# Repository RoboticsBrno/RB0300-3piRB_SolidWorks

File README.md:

# SOČ 2016 - Nadstavbová deska pro robota Pololu 3pi
**Autor:** Petr Bobčík

Vítejte v příloze mé práce Nadstavbová deska pro robota Pololu 3pi

#### V této příloze naleznete: 
1) Dokumenty
1) Eagle
1) Obhajoba
1) Použité obrázky
1) SolidWorks

#### Podrobnější obsah jednotlivých složek:
1) Přehled projektu s grafm pro IR senzor, obrázek s konceptem zapojení a tabulku potřebných součástek na pájení.
2) Finální verze desky a schéma k ní v programu Eagle + schéma s deskou k nárazovému senzoru.
3) Text samotné sočky a prezentaci k ní.
4) Veškeré obrázky použity jak v prezentaci, tak v textové práci.
5) Kompletní 3D model robota Pololu 3pi s přídavným shieldem.

## Cíl práce
<p>Cílem této práce byl návrh nadstavbové desky (shieldu) pro robota Pololu 3pi. Konstrukce robota je od výrobce optimalizována
na soutěžní disciplínu „sledování čáry“, kde robot dosahuje výborných výsledků a nemá mezi komerčně dostupnými produkty konkurenci. Ovšem při složitější variantě této disciplíny “najdi čáru“, konající se na Robotickém dni v Praze, kde dráha obsahuje rozpojky, odbočky, nebo překážky, není možné s ním závodit. Můj shield může posloužit, kromě možné účasti na soutěžích, také ve výuce. V ní si student může
robota sám naprogramovat. Přidáním funkcí a senzorů bude robot univerzálnější než doposud.</p>

<p>Práce řeší rozšíření možností využití robota Pololu 3pi návrhem nadstavby s doplňkovými funkcemi.
Přidané funkce umožňují robotovi snímat podněty ze svého okolí. Další navrženou částí je nárazník pro ochranu před mechanickým poškozením, ke kterému v praxi velmi často dochází. Tyto nárazy způsobovli nefunkčnost senzorů odrazivosti nebo dokonce i jejich odlomení od desky.</p>

Můj přídavný shield je také pinově kompatibilní s bastlířskými deskami, jako je **Arduino Uno**, **FRDM-KL25Z**, **FRDM-KL46Z** a **FRDM-K64F**. Je tedy možné a plánované, že pro přidání dalších funkcí, které můj shield neobsahuje, je možné připevnit jednu ze zmíněných desek, nebo desku, která má shodný pinout. Mikrokontroler, ATmega328P, který je na základním modelu robota se využívá jako MCU pro motory a hlavní řídící mikrokontroler je AVR XMEGu A1, který se nachází na mém shieldu. Ten mi poskytuje velký počet pinů s potřebnými periferiemi. 

## Jaké funkce jsou prostřednictvím shieldu přidány?
<p>Tato práce přidává robotovi Pololu 3pi schopnost detekovat překážku pomocí IR senzorů, kterých je na shieldu celkem 8 po 45° nebo pomocí nárazového senzoru, upevněného na mnou navržený nárazník. Dále také k orientaci v prostoru je přidáno IMU (inerciální pohybová jednotka), která obsahuje gyroskop, magnetometr a akcelerometr v jednom pouzdře. Posledním senzorem je enkodér, pomocí kterého můžeme měřit ujetou vzdálenost, zajišťuje přesnější otáčení okolo osi a umožňuje také měřit rychlost.</p><p>Na desce je přidán také chip pro nabíjení baterií, takže není zapotřebí vytahovat tužkové baterie, které se na základní verzi robota nacházejí. Pouzdra s tužkovými bateriemi je tedy možné vytáhnout a tím snížit váhu. Shield také obsahuje obvod pro měření baterie a to jak napětí, tak proudu. Tímto měřením je možné hlídat úroveň nabití baterie nebo dokonce detekovat, zda baterie není poškozená.</p>

## Co je vlastě Pololu 3pi? 
<p>Je to velmi rychlý komerčně dostupný soutěžní robot, určený na disciplínu s názvem sledování čáry, která je v České republice velmi populární (tato disciplína je více popsaná níže). Jeho průměr je 95 mm (odtud dostal název 3pi) a hmotnost 83 g (bez baterií). Jeho rychlost se pohybuje okolo 1m/s. Hlavním mozkem celého robota je mikrokontrolér ATmega328P, který se nachází například u Arduino Nano. Tento robot je vhodný pro začínající programátory, kteří se chtějí od začátečních robotů, jako například legových ze stavebnice Mindstorm, posunout o kousek dále a chtějí se naučit programovací.</p>

## Sledování čáry
</p>Úkolem robota je, aby následoval černou čářu, která se pod ním nachází. Nejprve šlo jen o jízdu po čáře, ale v poslední době se zmíněná disciplína výrazně ztížila, přidáním rozdvojení, křižovatky, přerušení a překážky. Pololu 3pi nedokáže tyto nové prvky řešit, a proto jsem se rozhodl přidat potřebné funkce, které to zajistí.<p>

#### [Více informací naleznete na stránkách Robotárny k mojí SOČ](https://www.robotikabrno.cz/robotarna/projekty-a-socky/soc-2017-petr-bobcik-nadstavbova-deska-pro-robota-pololu-3pi). 

Tato práce byla vypracována společně s [Robotárnou](www.robotarna.cz) a [SPŠ a VOŠ Sokolská Brno](www.spssbrno.cz).

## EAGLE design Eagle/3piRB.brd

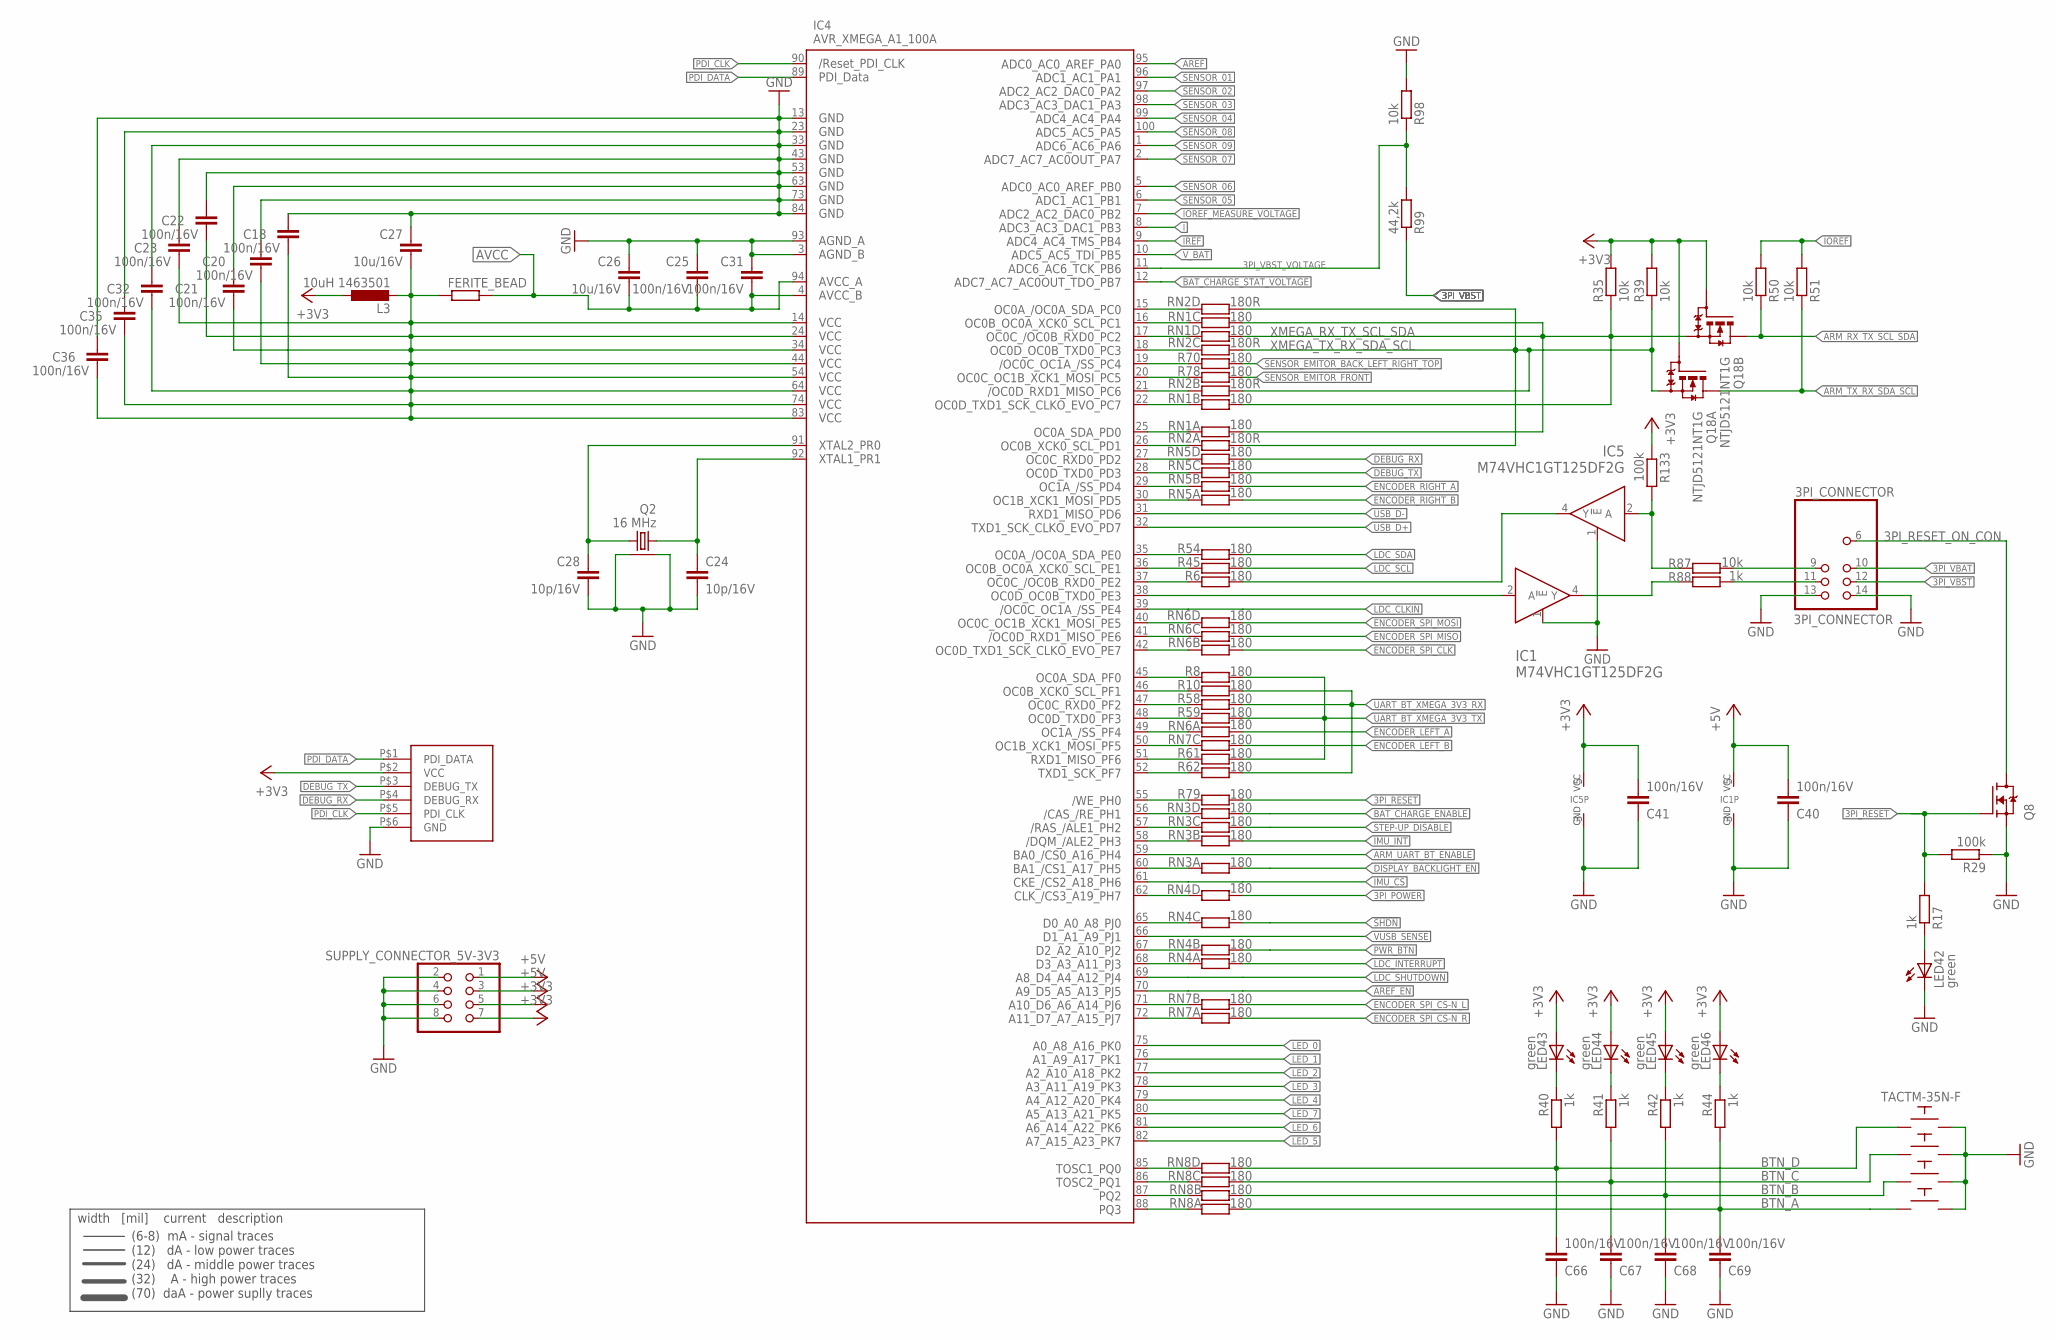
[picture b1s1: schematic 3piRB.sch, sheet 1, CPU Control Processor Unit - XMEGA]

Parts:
3PI_CONNECTOR: 3PI_CONNECTOR; 3PI_BT_CONNECTOR
BTN_A: TACTM-35N-F
BTN_B: TACTM-35N-F
BTN_C: TACTM-35N-F
BTN_D: TACTM-35N-F
C18, C20, C21, C22, C23, C25, C31, C32, C35, C36, C40, C41, C66, C67, C68, C69: 100n/16V; C0402
C24, C28: 10p/16V; C0603
C26, C27: 10u/16V; C0805
FERITE_BEAD: R-EU_R0603; R0603
IC1, IC5: M74VHC1GT125DF2G; SOT353
IC4: AVR_XMEGA_A1_100A; TQFP100
JP3: CON_PROG-6SMD; SMD-6
L3: 10uH 1463501; R0603
LED42, LED43, LED44, LED45, LED46: green; CHIPLED_0603
Q2: 16 MHz; ABM8
Q8: N-MOSFET-SOT323-GSD; SOT323
Q18: NTJD5121NT1G; SOT363
R6, R8, R10, R45, R54, R58, R59, R61, R62, R70, R78, R79: 180; _0402MP
R17, R40, R41, R42, R44, R88: 1k; _0402MP
R29, R133: 100k; _0402MP
R35, R39, R50, R51, R87, R98: 10k; _0402MP
R99: 44,2k; _0402MP
RN1, RN3, RN4, RN5, RN6, RN7, RN8: 180; 742-8
RN2: 180R; 742-8
SUPPLY_CONNECTOR_5V-3V3: PINHD-2X4; 2X04

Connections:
3PI-POWER: IC4.56 (PH1), RN3.4 (1)
3PI_POWER: RN4.5 (2); also elsewhere on the board
3PI_RESET: Q8.1 (G), R17.2, R29.2, R79.2
3PI_RESET_: IC4.55 (PH0), R79.1
3PI_RESET_ON_CON: 3PI_CONNECTOR.6, Q8.3 (D)
3PI_VBAT: 3PI_CONNECTOR.10; also elsewhere on the board
3PI_VBST: 3PI_CONNECTOR.12, R99.1; also elsewhere on the board
3PI_VBST_VOLTAGE: IC4.11 (PB6), R98.1, R99.2
3V3-L3-VCC_XMEGA: C18.2, C20.2, C21.2, C22.2, C23.2, C27.2, C32.2, C35.2, C36.2, FERITE_BEAD.2, IC4.14 (VCC1), IC4.24 (VCC2), IC4.34 (VCC3), IC4.44 (VCC4), IC4.54 (VCC5), IC4.64 (VCC6), IC4.74 (VCC7), IC4.83 (VCC8), L3.2
!SHDN: RN4.6 (2); also elsewhere on the board
+3V3: C41.2, IC5.5 (VCC), JP3.P$2 (VCC), L3.1, LED43.A, LED44.A, LED45.A, LED46.A, Q18.2 (G), Q18.5 (G), R35.2, R39.2, R133.1, SUPPLY_CONNECTOR_5V-3V3.5, SUPPLY_CONNECTOR_5V-3V3.7; also elsewhere on the board
+5V: C40.2, IC1.5 (VCC), SUPPLY_CONNECTOR_5V-3V3.1, SUPPLY_CONNECTOR_5V-3V3.3; also elsewhere on the board
AREF: IC4.95 (PA0); also elsewhere on the board
AREF_EN: IC4.70 (PJ5); also elsewhere on the board
ARM_RX_TX_SCL_SDA: Q18.3 (D), R50.1; also elsewhere on the board
ARM_TX_RX_SDA_SCL: Q18.6 (D), R51.1; also elsewhere on the board
ARM_UART_BT_ENABLE: IC4.59 (PH4); also elsewhere on the board
AVCC: C25.2, C26.2, C31.2, FERITE_BEAD.1, IC4.4 (AVCC_B), IC4.94 (AVCC_A); also elsewhere on the board
BAT_CHARGE_ENABLE: RN3.5 (2); also elsewhere on the board
BAT_CHARGE_ENABLE-A: IC4.62 (PH7), RN4.4 (1)
BAT_CHARGE_STAT_VOLTAGE: IC4.12 (PB7); also elsewhere on the board
BTN_A: BTN_A.P$2, C69.2, R44.2, RN8.8 (2)
BTN_A_: IC4.88 (PQ3), RN8.1
BTN_B: BTN_B.P$2, C68.2, R42.2, RN8.7 (2)
BTN_B_: IC4.87 (PQ2), RN8.2 (1)
BTN_C: BTN_C.P$2, C67.2, R41.2, RN8.6 (2)
BTN_C_: IC4.86 (PQ1), RN8.3 (1)
BTN_D: BTN_D.P$2, C66.2, R40.2, RN8.5 (2)
BTN_D_: IC4.85 (PQ0), RN8.4 (1)
DEBUG_RX: JP3.P$4 (DEBUG_RX), RN5.5 (2)
DEBUG_RX_: IC4.27 (PD2), RN5.4 (1)
DEBUG_TX: JP3.P$3 (DEBUG_TX), RN5.6 (2)
DEBUG_TX_: IC4.28 (PD3), RN5.3 (1)
DISPLAY_BACKLIGHT-EN: IC4.65 (PJ0), RN4.3 (1)
DISPLAY_BACKLIGHT_EN: RN3.8 (2); also elsewhere on the board
ENCODER_LEFT_A: RN6.8 (2); also elsewhere on the board
ENCODER_LEFT_A_: IC4.29 (PD4), RN5.2 (1)
ENCODER_LEFT_B: RN7.6 (2); also elsewhere on the board
ENCODER_LEFT_B_: IC4.30 (PD5), RN5.1
ENCODER_RIGHT_A: RN5.7 (2); also elsewhere on the board
ENCODER_RIGHT_A_: IC4.49 (PF4), RN6.1
ENCODER_RIGHT_B: RN5.8 (2); also elsewhere on the board
ENCODER_RIGHT_B_: IC4.50 (PF5), RN7.3 (1)
ENCODER_SPI_CLK: RN6.7 (2); also elsewhere on the board
ENCODER_SPI_CLK_: IC4.42 (PE7), RN6.2 (1)
ENCODER_SPI_CS-N_L: RN7.7 (2); also elsewhere on the board
ENCODER_SPI_CS-N_L_: IC4.71 (PJ6), RN7.2 (1)
ENCODER_SPI_CS-N_R: RN7.8 (2); also elsewhere on the board
ENCODER_SPI_CS-N_R_: IC4.72 (PJ7), RN7.1
ENCODER_SPI_MISO: RN6.6 (2); also elsewhere on the board
ENCODER_SPI_MISO_: IC4.41 (PE6), RN6.3 (1)
ENCODER_SPI_MOSI: RN6.5 (2); also elsewhere on the board
ENCODER_SPI_MOSI_: IC4.40 (PE5), RN6.4 (1)
GND: 3PI_CONNECTOR.13, 3PI_CONNECTOR.14, BTN_A.P$4, BTN_B.P$4, BTN_C.P$4, BTN_D.P$4, C18.1, C20.1, C21.1, C22.1, C23.1, C24.2, C25.1, C26.1, C27.1, C28.2, C31.1, C32.1, C35.1, C36.1, C40.1, C41.1, C66.1, C67.1, C68.1, C69.1, IC1.1 (!E), IC1.3 (GND), IC4.3 (AGND_B), IC4.13 (GND1), IC4.23 (GND2), IC4.33 (GND3), IC4.43 (GND4), IC4.53 (GND5), IC4.63 (GND6), IC4.73 (GND7), IC4.84 (GND8), IC4.93 (AGND_A), IC5.1 (!E), IC5.3 (GND), JP3.P$6 (GND), LED42.C, Q2.GND$1, Q2.GND$2, Q8.2 (S), R29.1, R98.2, SUPPLY_CONNECTOR_5V-3V3.2, SUPPLY_CONNECTOR_5V-3V3.4, SUPPLY_CONNECTOR_5V-3V3.6, SUPPLY_CONNECTOR_5V-3V3.8; also elsewhere on the board
I: IC4.8 (PB3); also elsewhere on the board
IMU-ENT: IC4.58 (PH3), RN3.2 (1)
IMU_CS: IC4.61 (PH6); also elsewhere on the board
IMU_INT: RN3.7 (2); also elsewhere on the board
IOREF: R50.2, R51.2; also elsewhere on the board
IOREF_MEASURE_VOLTAGE: IC4.7 (PB2); also elsewhere on the board
IREF: IC4.9 (PB4); also elsewhere on the board
LDC_CLKIN: IC4.39 (PE4); also elsewhere on the board
LDC_INTERRUPT: RN4.8 (2); also elsewhere on the board
LDC_INTERRUPT_: IC4.68 (PJ3), RN4.1
LDC_SCL: R45.1; also elsewhere on the board
LDC_SCL_: IC4.36 (PE1), R45.2
LDC_SDA: R54.1; also elsewhere on the board
LDC_SDA_: IC4.35 (PE0), R54.2
LDC_SHUTDOWN: IC4.69 (PJ4); also elsewhere on the board
LED_0: IC4.75 (PK0); also elsewhere on the board
LED_1: IC4.76 (PK1); also elsewhere on the board
LED_2: IC4.77 (PK2); also elsewhere on the board
LED_3: IC4.78 (PK3); also elsewhere on the board
LED_4: IC4.79 (PK4); also elsewhere on the board
LED_5: IC4.82 (PK7); also elsewhere on the board
LED_6: IC4.81 (PK6); also elsewhere on the board
LED_7: IC4.80 (PK5); also elsewhere on the board
LED_R_20: LED42.A, R17.1
unnamed: LED43.C, R40.1
unnamed: LED44.C, R41.1
unnamed: LED45.C, R42.1
unnamed: LED46.C, R44.1
PDI_CLK: IC4.90 (RESET), JP3.P$5 (PDI_CLK)
PDI_DATA: IC4.89 (PDI_DATA), JP3.P$1 (PDI_DATA)
PWR_BTN: RN4.7 (2); also elsewhere on the board
PWR_BTN_: IC4.57 (PH2), RN3.3 (1)
SENSOR_01: IC4.96 (PA1); also elsewhere on the board
SENSOR_02: IC4.97 (PA2); also elsewhere on the board
SENSOR_03: IC4.98 (PA3); also elsewhere on the board
SENSOR_04: IC4.99 (PA4); also elsewhere on the board
SENSOR_05: IC4.6 (PB1); also elsewhere on the board
SENSOR_06: IC4.5 (PB0); also elsewhere on the board
SENSOR_07: IC4.2 (PA7); also elsewhere on the board
SENSOR_08: IC4.100 (PA5); also elsewhere on the board
SENSOR_09: IC4.1 (PA6); also elsewhere on the board
SENSOR_EMITOR_BACK_LEFT_RIGHT_TOP: R70.2; also elsewhere on the board
SENSOR_EMITOR_BACK_LEFT_RIGHT_TOP_: IC4.20 (PC5), R78.1
SENSOR_EMITOR_FRONT: R78.2; also elsewhere on the board
SENSOR_EMITOR_FRONT_: IC4.19 (PC4), R70.1
SHDN_: IC4.67 (PJ2), RN4.2 (1)
STEP-UP_DISABLE: RN3.6 (2); also elsewhere on the board
STEP-UP_DISABLE_: IC4.60 (PH5), RN3.1
UART_3V3_3PI_RX: IC5.4 (Y), R6.2
UART_3V3_3PI_RX_: IC4.37 (PE2), R6.1
UART_3V3_3PI_TX: IC1.2 (A), IC4.38 (PE3)
UART_5V_3PI_RX: IC5.2 (A), R87.1, R133.2
UART_5V_3PI_RX_J: 3PI_CONNECTOR.9, R87.2
UART_5V_3PI_TX: IC1.4 (Y), R88.1
UART_5V_3PI_TX_J: 3PI_CONNECTOR.11, R88.2
UART_BT_XMEGA_3V3_RX: R10.2, R58.2, R62.2; also elsewhere on the board
UART_BT_XMEGA_3V3_RX_PF1-SCL: IC4.46 (PF1), R10.1
UART_BT_XMEGA_3V3_RX_PF2-RXD0: IC4.47 (PF2), R58.1
UART_BT_XMEGA_3V3_RX_PF7-TXD1: IC4.52 (PF7), R62.1
UART_BT_XMEGA_3V3_TX: R8.2, R59.2, R61.2; also elsewhere on the board
UART_BT_XMEGA_3V3_TX_PF0-SDA: IC4.45 (PF0), R8.1
UART_BT_XMEGA_3V3_TX_PF3-TXD0: IC4.48 (PF3), R59.1
UART_BT_XMEGA_3V3_TX_PF6-RXD1: IC4.51 (PF6), R61.1
USB_D+: IC4.32 (PD7); also elsewhere on the board
USB_D-: IC4.31 (PD6); also elsewhere on the board
VUSB_SENSE: IC4.66 (PJ1); also elsewhere on the board
V_BAT: IC4.10 (PB5); also elsewhere on the board
XMEGA_RX_TX_SCL_SDA: Q18.4 (S), R35.1, RN1.5 (2), RN1.6 (2), RN1.7 (2), RN1.8 (2)
XMEGA_RX_TX_SCL_SDA_PC1-SCL: IC4.16 (PC1), RN1.3 (1)
XMEGA_RX_TX_SCL_SDA_PC2-RXD0: IC4.17 (PC2), RN1.4 (1)
XMEGA_RX_TX_SCL_SDA_PC7-TXD1: IC4.22 (PC7), RN1.2 (1)
XMEGA_RX_TX_SCL_SDA_PD0-SDA: IC4.25 (PD0), RN1.1
XMEGA_TX_RX_SDA_SCL: Q18.1 (S), R39.1, RN2.5 (2), RN2.6 (2), RN2.7 (2), RN2.8 (2)
XMEGA_TX_RX_SDA_SCL_PC0-SDA: IC4.15 (PC0), RN2.4 (1)
XMEGA_TX_RX_SDA_SCL_PC3-TXD0: IC4.18 (PC3), RN2.3 (1)
XMEGA_TX_RX_SDA_SCL_PC6-RXD1: IC4.21 (PC6), RN2.2 (1)
XMEGA_TX_RX_SDA_SCL_PD1-SCL: IC4.26 (PD1), RN2.1
XTAL1: C24.1, IC4.92 (PR1), Q2.Q$1 (1)
XTAL2: C28.1, IC4.91 (PR0), Q2.Q$2 (2)

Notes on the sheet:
(6-8) mA - signal traces (12) dA - low power traces (24) dA - middle power traces (32) A - high power traces (70) daA - power suplly traces
width [mil] current description

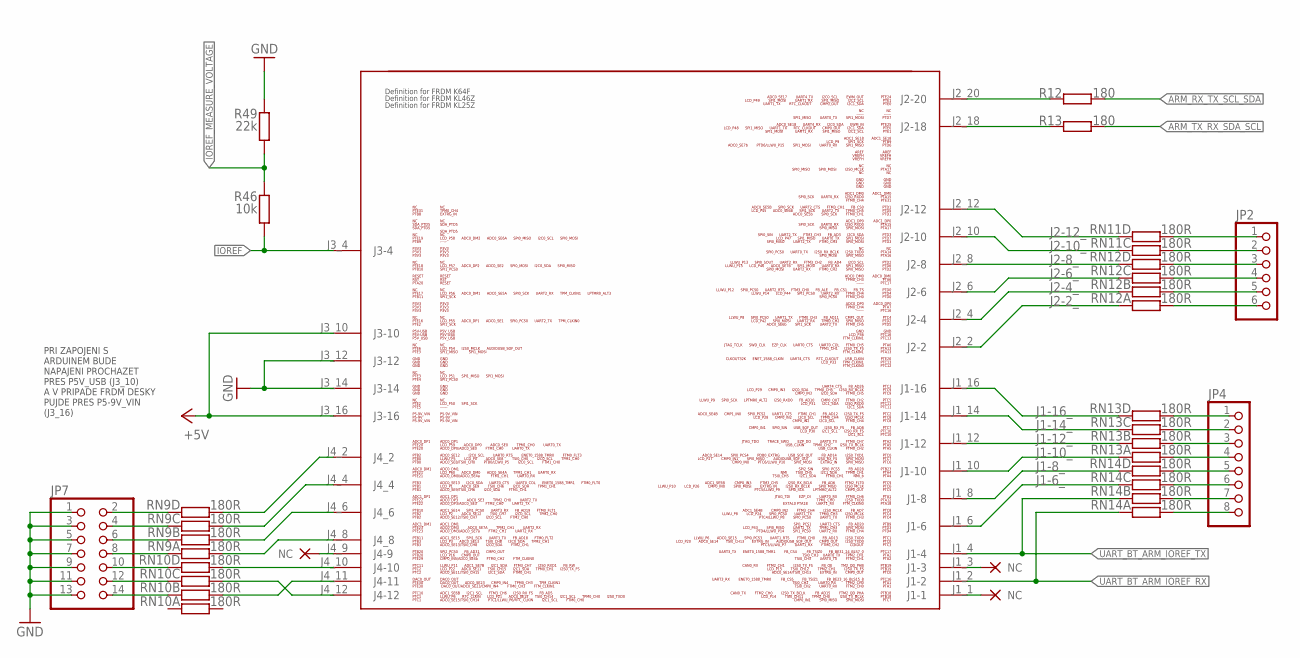
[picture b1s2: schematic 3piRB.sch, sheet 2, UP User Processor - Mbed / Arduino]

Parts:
JP2: PINHD-1X6; 1X06
JP4: PINHD-1X8; 1X08
JP7: PINHD-2X7; 2X07
R12, R13: 180; _0402MP
R46: 10k; _0402MP
R49: 22k; _0402MP
RN9, RN10, RN11, RN12, RN13, RN14: 180R; 742-8
U$1: FRDM-KL25Z+KL46Z+K64F_MORE_PINS

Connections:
+5V: U$1.J3_10 (J3-10), U$1.J3_16 (J3-16); also elsewhere on the board
ARM_RX_TX_SCL_SDA: R12.2; also elsewhere on the board
ARM_RX_TX_SCL_SDA_: R12.1, U$1.J2_20 (J2-20)
ARM_TX_RX_SDA_SCL: R13.2; also elsewhere on the board
ARM_TX_RX_SDA_SCL_: R13.1, U$1.J2_18 (J2-18)
GND: JP7.1, JP7.3, JP7.5, JP7.7, JP7.9, JP7.11, JP7.13, R49.2, U$1.J3_12 (J3-12), U$1.J3_14 (J3-14); also elsewhere on the board
IOREF: R46.1, U$1.J3_4 (J3-4); also elsewhere on the board
IOREF_MEASURE_VOLTAGE: R46.2, R49.1; also elsewhere on the board
J1-2: JP4.8, RN14.8 (2)
J1-4: JP4.7, RN14.7 (2)
J1-6: JP4.6, RN14.6 (2)
J1-6_: RN14.3 (1), U$1.J1_6 (J1-6)
J1-8: JP4.5, RN14.5 (2)
J1-8_: RN14.4 (1), U$1.J1_8 (J1-8)
J1-10: JP4.4, RN13.8 (2)
J1-10_: RN13.1, U$1.J1_10 (J1-10)
J1-12: JP4.3, RN13.7 (2)
J1-12_: RN13.2 (1), U$1.J1_12 (J1-12)
J1-14: JP4.2, RN13.6 (2)
J1-14_: RN13.3 (1), U$1.J1_14 (J1-14)
J1-16: JP4.1, RN13.5 (2)
J1-16_: RN13.4 (1), U$1.J1_16 (J1-16)
J2-2: JP2.6, RN12.8 (2)
J2-2_: RN12.1, U$1.J2_2 (J2-2)
J2-4: JP2.5, RN12.7 (2)
J2-4_: RN12.2 (1), U$1.J2_4 (J2-4)
J2-6: JP2.4, RN12.6 (2)
J2-6_: RN12.3 (1), U$1.J2_6 (J2-6)
J2-8: JP2.3, RN12.5 (2)
J2-8_: RN12.4 (1), U$1.J2_8 (J2-8)
J2-10: JP2.2, RN11.6 (2)
J2-10_: RN11.3 (1), U$1.J2_10 (J2-10)
J2-12: JP2.1, RN11.5 (2)
J2-12_: RN11.4 (1), U$1.J2_12 (J2-12)
J4-2: JP7.2, RN9.4 (1)
J4-2_: RN9.5 (2), U$1.J4_2
J4-4: JP7.4, RN9.3 (1)
J4-4_: RN9.6 (2), U$1.J4_4
J4-6: JP7.6, RN9.2 (1)
J4-6_: RN9.7 (2), U$1.J4_6
J4-8: JP7.8, RN9.1
J4-8_: RN9.8 (2), U$1.J4_8
J4-10: JP7.10, RN10.4 (1)
J4-10_: RN10.5 (2), U$1.J4_10 (J4-10)
J4-11: JP7.14, RN10.2 (1)
J4-11_: RN10.7 (2), U$1.J4_11 (J4-11)
J4-12: JP7.12, RN10.3 (1)
J4-12_: RN10.6 (2), U$1.J4_12 (J4-12)
UART_BT_ARM_IOREF_RX: RN14.1, U$1.J1_2 (J1-2); also elsewhere on the board
UART_BT_ARM_IOREF_TX: RN14.2 (1), U$1.J1_4 (J1-4); also elsewhere on the board

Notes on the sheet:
PRI ZAPOJENI S ARDUINEM BUDE NAPAJENI PROCHAZET PRES P5V_USB (J3_10) A V PRIPADE FRDM DESKY PUJDE PRES P5-9V_VIN (J3_16)

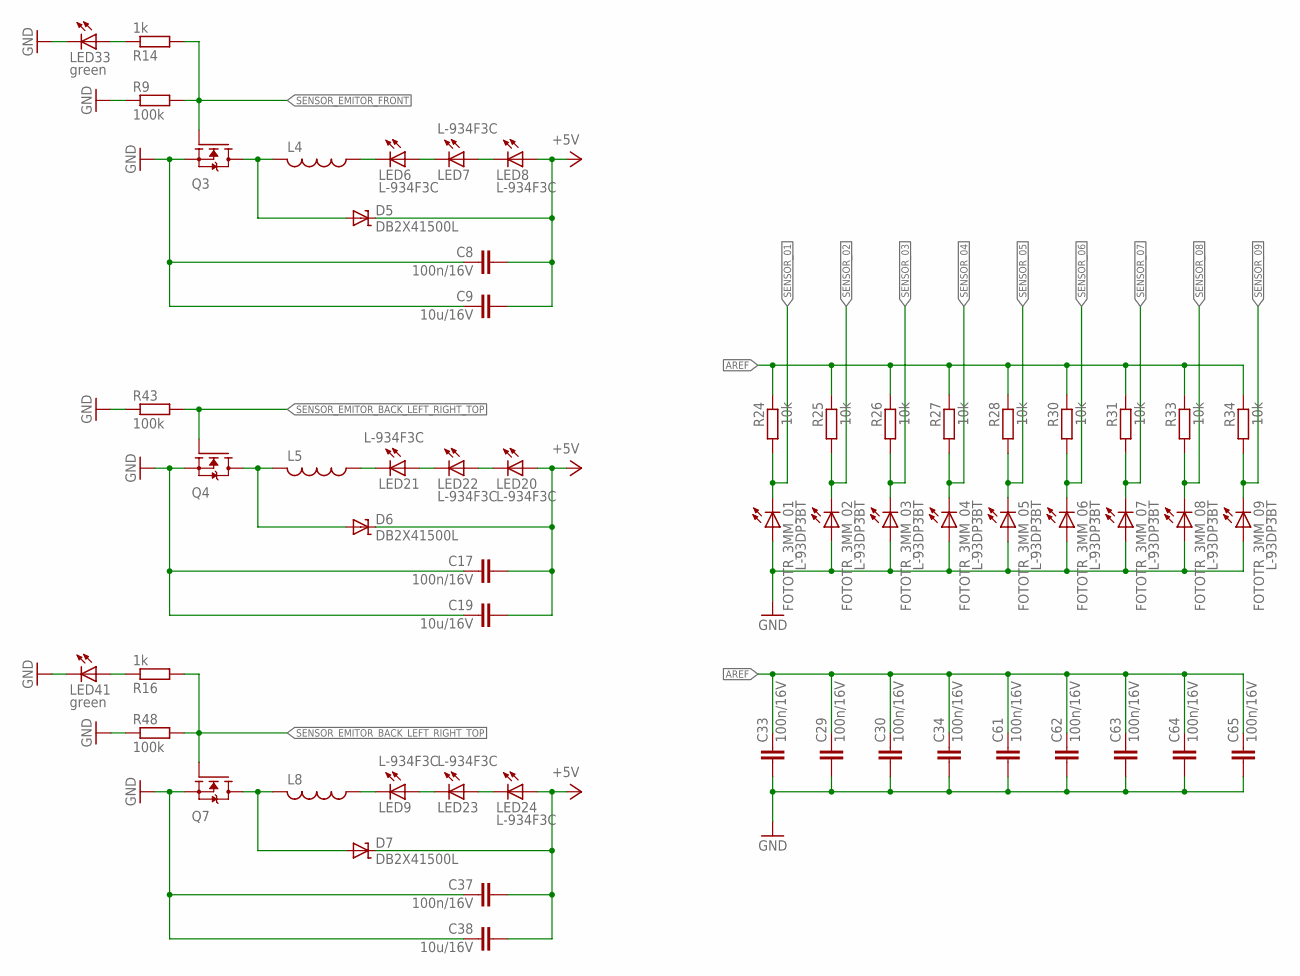
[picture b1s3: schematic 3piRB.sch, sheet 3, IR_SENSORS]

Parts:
C8, C17, C29, C30, C33, C34, C37, C61, C62, C63, C64, C65: 100n/16V; C0402
C9, C19, C38: 10u/16V; C0805
D5, D6, D7: DB2X41500L; SOD123
FOTOTR_3MM_01, FOTOTR_3MM_02, FOTOTR_3MM_03, FOTOTR_3MM_04, FOTOTR_3MM_05, FOTOTR_3MM_06, FOTOTR_3MM_07, FOTOTR_3MM_08, FOTOTR_3MM_09: L-93DP3BT; LED3MM
L4, L5, L8: L-USL0805; R0805@1
LED6, LED7, LED8, LED9, LED20, LED21, LED22, LED23, LED24: L-934F3C; LED3MM
LED33, LED41: green; CHIPLED_0603
Q3, Q4, Q7: N-MOSFET-SOT323-GSD; SOT323
R9, R43, R48: 100k; _0402MP
R14, R16: 1k; _0402MP
R24, R25, R26, R27, R28, R30, R31, R33, R34: 10k; _0402MP

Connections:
+5V: C8.1, C9.1, C17.1, C19.1, C37.1, C38.1, D5.C, D6.C, D7.C, LED8.A, LED20.A, LED24.A; also elsewhere on the board
AREF: C29.2, C30.2, C33.2, C34.2, C61.2, C62.2, C63.2, C64.2, C65.2, R24.1, R25.1, R26.1, R27.1, R28.1, R30.1, R31.1, R33.1, R34.1; also elsewhere on the board
GND: C8.2, C9.2, C17.2, C19.2, C29.1, C30.1, C33.1, C34.1, C37.2, C38.2, C61.1, C62.1, C63.1, C64.1, C65.1, FOTOTR_3MM_01.A, FOTOTR_3MM_02.A, FOTOTR_3MM_03.A, FOTOTR_3MM_04.A, FOTOTR_3MM_05.A, FOTOTR_3MM_06.A, FOTOTR_3MM_07.A, FOTOTR_3MM_08.A, FOTOTR_3MM_09.A, LED33.C, LED41.C, Q3.2 (S), Q4.2 (S), Q7.2 (S), R9.1, R43.1, R48.1; also elsewhere on the board
LED_R_8: LED33.A, R14.1
LED_R_19: LED41.A, R16.1
unnamed: LED20.K (C), LED22.A
unnamed: LED21.A, LED22.K (C)
unnamed: L5.1, LED21.K (C)
SENSOR_01: FOTOTR_3MM_01.K (C), R24.2; also elsewhere on the board
SENSOR_02: FOTOTR_3MM_02.K (C), R25.2; also elsewhere on the board
SENSOR_03: FOTOTR_3MM_03.K (C), R26.2; also elsewhere on the board
SENSOR_04: FOTOTR_3MM_04.K (C), R27.2; also elsewhere on the board
SENSOR_05: FOTOTR_3MM_05.K (C), R28.2; also elsewhere on the board
SENSOR_06: FOTOTR_3MM_06.K (C), R30.2; also elsewhere on the board
SENSOR_07: FOTOTR_3MM_07.K (C), R31.2; also elsewhere on the board
SENSOR_08: FOTOTR_3MM_08.K (C), R33.2; also elsewhere on the board
SENSOR_09: FOTOTR_3MM_09.K (C), R34.2; also elsewhere on the board
SENSOR_EMITORLEFT_RIGHT_TOP_COIL: D7.A, L8.2, Q7.3 (D)
SENSOR_EMITORLEFT_RIGHT_TOP_L0: L8.1, LED9.K (C)
SENSOR_EMITORLEFT_RIGHT_TOP_L1: LED9.A, LED23.K (C)
SENSOR_EMITORLEFT_RIGHT_TOP_L2: LED23.A, LED24.K (C)
SENSOR_EMITOR_BACK_COIL: D6.A, L5.2, Q4.3 (D)
SENSOR_EMITOR_BACK_LEFT_RIGHT_TOP: Q4.1 (G), Q7.1 (G), R16.2, R43.2, R48.2; also elsewhere on the board
SENSOR_EMITOR_FRONT: Q3.1 (G), R9.2, R14.2; also elsewhere on the board
SENSOR_EMITOR_FRONT_COIL: D5.A, L4.2, Q3.3 (D)
SENSOR_EMITOR_FRONT_L0: L4.1, LED6.K (C)
SENSOR_EMITOR_FRONT_L1: LED6.A, LED7.K (C)
SENSOR_EMITOR_FRONT_L2: LED7.A, LED8.K (C)

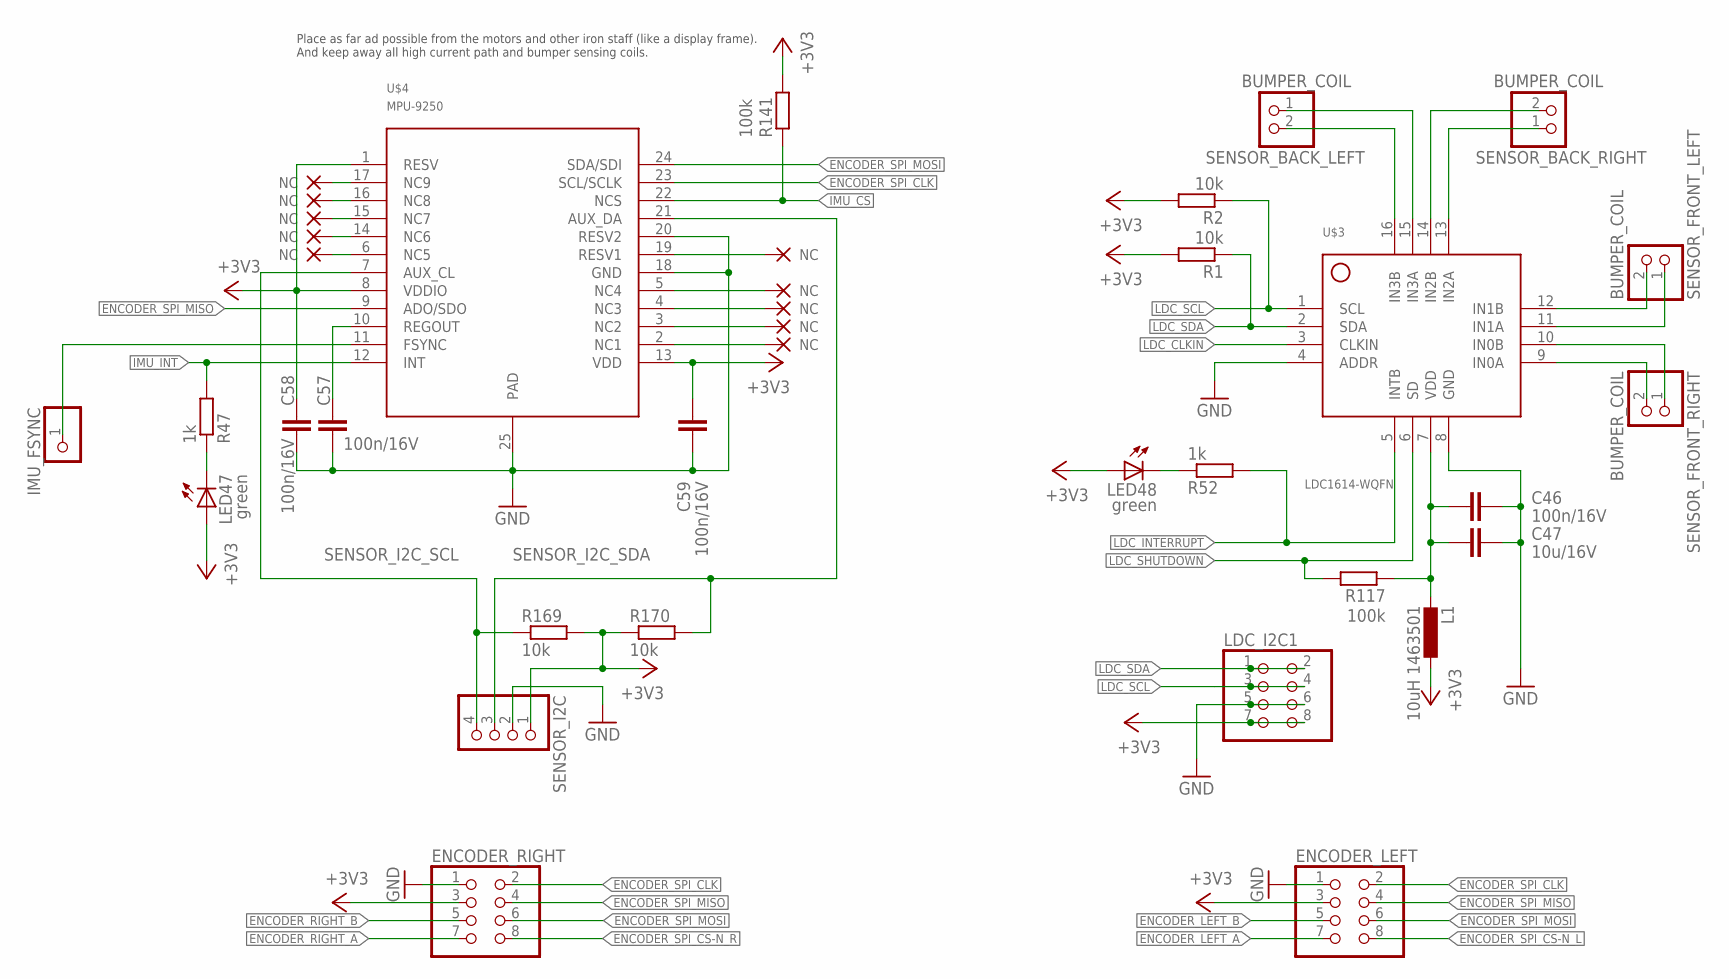
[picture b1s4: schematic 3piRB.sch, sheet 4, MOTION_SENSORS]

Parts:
C46, C57, C58, C59: 100n/16V; C0402
C47: 10u/16V; C0805
ENCODER_LEFT: PINHD-2X4; 2X04
ENCODER_RIGHT: PINHD-2X4; 2X04
IMU_FSYNC: PINHD-1X1; 1X01
L1: 10uH 1463501; R0603
LDC_I2C1: PINHD-2X4; 2X04
LED47, LED48: green; CHIPLED_0603
R1, R2, R169, R170: 10k; _0402MP
R47, R52: 1k; _0402MP
R117, R141: 100k; _0402MP
SENSOR_BACK_LEFT: BUMPER_COIL; 1X02
SENSOR_BACK_RIGHT: BUMPER_COIL; 1X02
SENSOR_FRONT_LEFT: BUMPER_COIL; 1X02
SENSOR_FRONT_RIGHT: BUMPER_COIL; 1X02
SENSOR_I2C: PINHD-1X4; 1X04
U$3: LDC1614-WQFN
U$4: MPU-9250; LEAD-QFN24

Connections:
+3V3: C58.1, C59.2, ENCODER_LEFT.3, ENCODER_RIGHT.3, L1.1, LDC_I2C1.7, LDC_I2C1.8, LED47.A, LED48.A, R1.2, R2.2, R141.2, R169.2, R170.1, SENSOR_I2C.1, U$4.1 (RESV), U$4.8 (VDDIO), U$4.13 (VDD); also elsewhere on the board
BUMPER_BACK_LEFT_A: SENSOR_BACK_LEFT.1, U$3.15 (IN3A)
BUMPER_BACK_LEFT_B: SENSOR_BACK_LEFT.2, U$3.16 (IN3B)
BUMPER_BACK_RIGHT_A: SENSOR_BACK_RIGHT.1, U$3.13 (IN2A)
BUMPER_BACK_RIGHT_B: SENSOR_BACK_RIGHT.2, U$3.14 (IN2B)
BUMPER_FRONT_LEFT_A: SENSOR_FRONT_LEFT.1, U$3.11 (IN1A)
BUMPER_FRONT_LEFT_B: SENSOR_FRONT_LEFT.2, U$3.12 (IN1B)
BUMPER_FRONT_RIGHT_A: SENSOR_FRONT_RIGHT.2, U$3.9 (IN0A)
BUMPER_FRONT_RIGHT_B: SENSOR_FRONT_RIGHT.1, U$3.10 (IN0B)
ENCODER_LEFT_A: ENCODER_LEFT.7; also elsewhere on the board
ENCODER_LEFT_B: ENCODER_LEFT.5; also elsewhere on the board
ENCODER_RIGHT_A: ENCODER_RIGHT.7; also elsewhere on the board
ENCODER_RIGHT_B: ENCODER_RIGHT.5; also elsewhere on the board
ENCODER_SPI_CLK: ENCODER_LEFT.2, ENCODER_RIGHT.2, U$4.23 (SCL/SCLK); also elsewhere on the board
ENCODER_SPI_CS-N_L: ENCODER_LEFT.8; also elsewhere on the board
ENCODER_SPI_CS-N_R: ENCODER_RIGHT.8; also elsewhere on the board
ENCODER_SPI_MISO: ENCODER_LEFT.4, ENCODER_RIGHT.4, U$4.9 (ADO/SDO); also elsewhere on the board
ENCODER_SPI_MOSI: ENCODER_LEFT.6, ENCODER_RIGHT.6, U$4.24 (SDA/SDI); also elsewhere on the board
GND: C46.2, C47.2, C57.1, C58.2, C59.1, ENCODER_LEFT.1, ENCODER_RIGHT.1, LDC_I2C1.5, LDC_I2C1.6, SENSOR_I2C.2, U$3.4 (ADDR), U$3.8 (GND), U$4.18 (GND), U$4.20 (RESV2), U$4.25 (PAD); also elsewhere on the board
IMU_CS: R141.1, U$4.22 (NCS); also elsewhere on the board
IMU_FSYNC: IMU_FSYNC.1, U$4.11 (FSYNC)
IMU_INT: R47.2, U$4.12 (INT); also elsewhere on the board
LDC_CLKIN: U$3.3 (CLKIN); also elsewhere on the board
LDC_INTERRUPT: R52.2, U$3.5 (INTB); also elsewhere on the board
LDC_PWR: C46.1, C47.1, L1.2, R117.1, U$3.7 (VDD)
LDC_SCL: LDC_I2C1.3, LDC_I2C1.4, R2.1, U$3.1 (SCL); also elsewhere on the board
LDC_SDA: LDC_I2C1.1, LDC_I2C1.2, R1.1, U$3.2 (SDA); also elsewhere on the board
LDC_SHUTDOWN: R117.2, U$3.6 (SD); also elsewhere on the board
unnamed: LED47.C, R47.1
unnamed: LED48.C, R52.1
NC_IMU_1: U$4.2 (NC1)
NC_IMU_2: U$4.3 (NC2)
NC_IMU_3: U$4.4 (NC3)
NC_IMU_4: U$4.5 (NC4)
NC_IMU_5: U$4.6 (NC5)
NC_IMU_6: U$4.14 (NC6)
NC_IMU_7: U$4.15 (NC7)
NC_IMU_8: U$4.16 (NC8)
NC_IMU_9: U$4.17 (NC9)
NC_IMU_RESV1: U$4.19 (RESV1)
REGOUT: C57.2, U$4.10 (REGOUT)
SENSOR_I2C_SCL: R169.1, SENSOR_I2C.4, U$4.7 (AUX_CL)
SENSOR_I2C_SDA: R170.2, SENSOR_I2C.3, U$4.21 (AUX_DA)

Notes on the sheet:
Place as far ad possible from the motors and other iron staff (like a display frame). And keep away all high current path and bumper sensing coils.

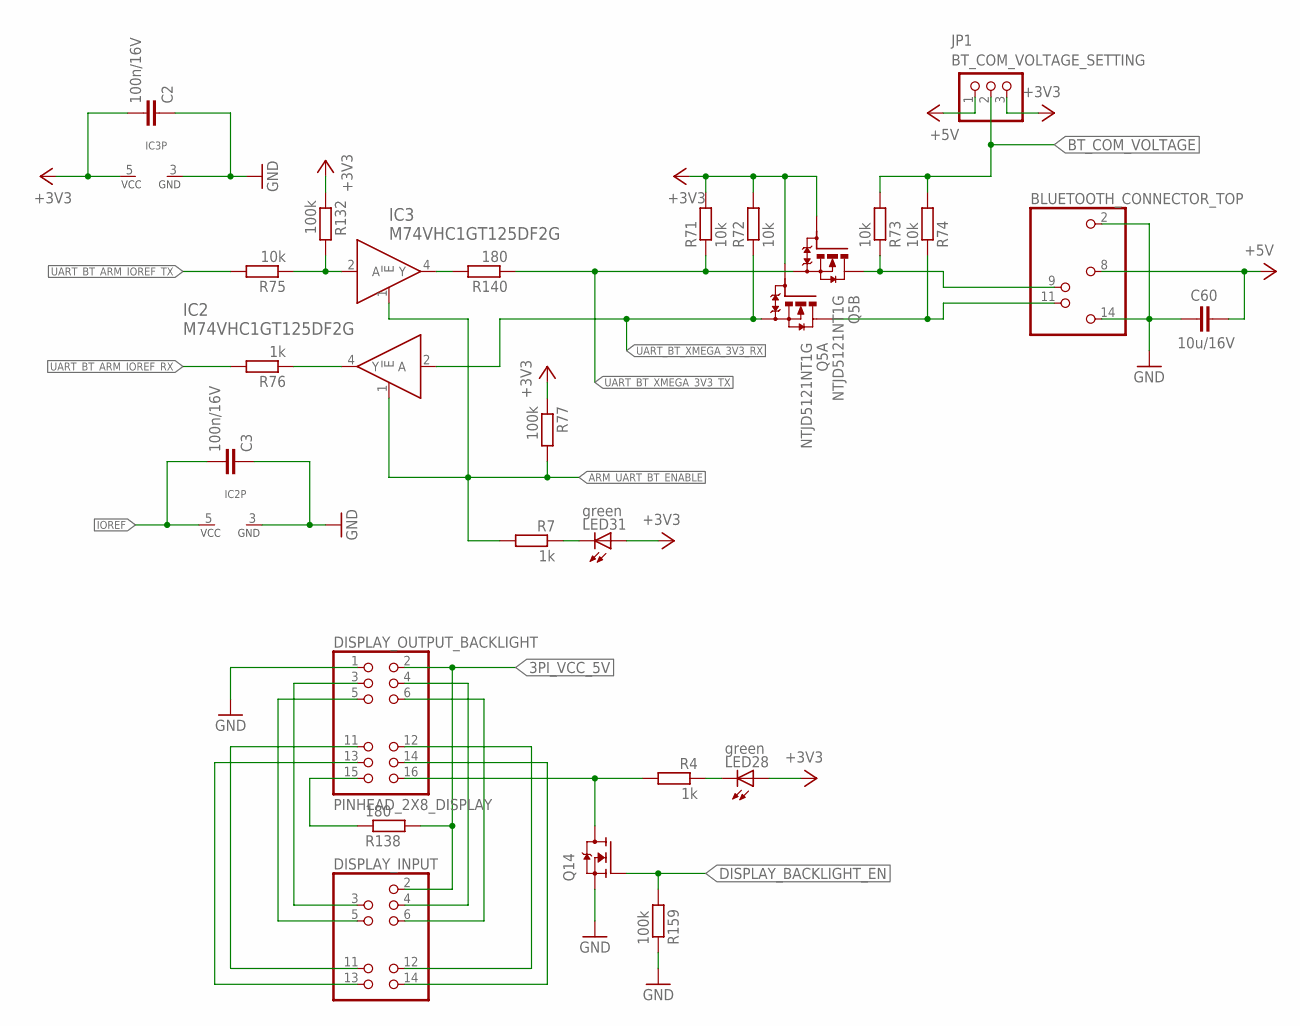
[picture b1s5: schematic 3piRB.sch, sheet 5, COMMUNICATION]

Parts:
BLUETOOTH_CONNECTOR_TOP: BLUETOOTH_CONNECTOR_TOP
C2, C3: 100n/16V; C0402
C60: 10u/16V; C0805
DISPLAY_INPUT: DISPLAY_INPUT
DISPLAY_OUTPUT_BACKLIGHT: PINHEAD_2X8_DISPLAY
IC2, IC3: M74VHC1GT125DF2G; SOT353
JP1: BT_COM_VOLTAGE_SETTING; 1X03
LED28, LED31: green; CHIPLED_0603
Q5: NTJD5121NT1G; SOT363
Q14: N-MOSFET-SOT323-GSD; SOT323
R4, R7, R76: 1k; _0402MP
R71, R72, R73, R74, R75: 10k; _0402MP
R77, R132, R159: 100k; _0402MP
R138, R140: 180; _0402MP

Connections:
3PI_VCC_5V: DISPLAY_INPUT.2, DISPLAY_OUTPUT_BACKLIGHT.2, R138.2; also elsewhere on the board
+3V3: C2.2, IC3.5 (VCC), JP1.3, LED28.A, LED31.A, Q5.2 (G), Q5.5 (G), R71.2, R72.2, R77.1, R132.1; also elsewhere on the board
+5V: BLUETOOTH_CONNECTOR_TOP.8, C60.2, JP1.1; also elsewhere on the board
ARM_UART_BT_ENABLE: IC2.1 (!E), IC3.1 (!E), R7.2, R77.2; also elsewhere on the board
BT_COM_VOLTAGE: JP1.2, R73.2, R74.2; also elsewhere on the board
DISPLAY_BACKLIGHT_EN: Q14.1 (G), R159.2; also elsewhere on the board
DISPLAY_BACKLIGHT_SW_GND: DISPLAY_OUTPUT_BACKLIGHT.16, Q14.3 (D), R4.2
DISPLAY_BACKLIGHT_VCC: DISPLAY_OUTPUT_BACKLIGHT.15, R138.1
DISPLAY_DB4: DISPLAY_INPUT.11, DISPLAY_OUTPUT_BACKLIGHT.11
DISPLAY_DB5: DISPLAY_INPUT.12, DISPLAY_OUTPUT_BACKLIGHT.12
DISPLAY_DB6: DISPLAY_INPUT.13, DISPLAY_OUTPUT_BACKLIGHT.13
DISPLAY_DB7: DISPLAY_INPUT.14, DISPLAY_OUTPUT_BACKLIGHT.14
DISPLAY_E: DISPLAY_INPUT.6, DISPLAY_OUTPUT_BACKLIGHT.6
DISPLAY_R!W: DISPLAY_INPUT.5, DISPLAY_OUTPUT_BACKLIGHT.5
DISPLAY_RS: DISPLAY_INPUT.4, DISPLAY_OUTPUT_BACKLIGHT.4
DISPLAY_V0: DISPLAY_INPUT.3, DISPLAY_OUTPUT_BACKLIGHT.3
GND: BLUETOOTH_CONNECTOR_TOP.2, BLUETOOTH_CONNECTOR_TOP.14, C2.1, C3.1, C60.1, DISPLAY_OUTPUT_BACKLIGHT.1, IC2.3 (GND), IC3.3 (GND), Q14.2 (S), R159.1; also elsewhere on the board
IOREF: C3.2, IC2.5 (VCC); also elsewhere on the board
unnamed: LED28.C, R4.1
unnamed: LED31.C, R7.1
UART_BT_5V_RX1: BLUETOOTH_CONNECTOR_TOP.11, Q5.6 (D), R74.1
UART_BT_5V_TX1: BLUETOOTH_CONNECTOR_TOP.9, Q5.3 (D), R73.1
UART_BT_ARM_IOREF-RX: IC2.4 (Y), R76.1
UART_BT_ARM_IOREF-TX: IC3.2 (A), R75.1, R132.2
UART_BT_ARM_IOREF_RX: R76.2; also elsewhere on the board
UART_BT_ARM_IOREF_TX: R75.2; also elsewhere on the board
UART_BT_XMEGA_3V3-TX: IC3.4 (Y), R140.2
UART_BT_XMEGA_3V3_RX: IC2.2 (A), Q5.1 (S), R72.1; also elsewhere on the board
UART_BT_XMEGA_3V3_TX: Q5.4 (S), R71.1, R140.1; also elsewhere on the board

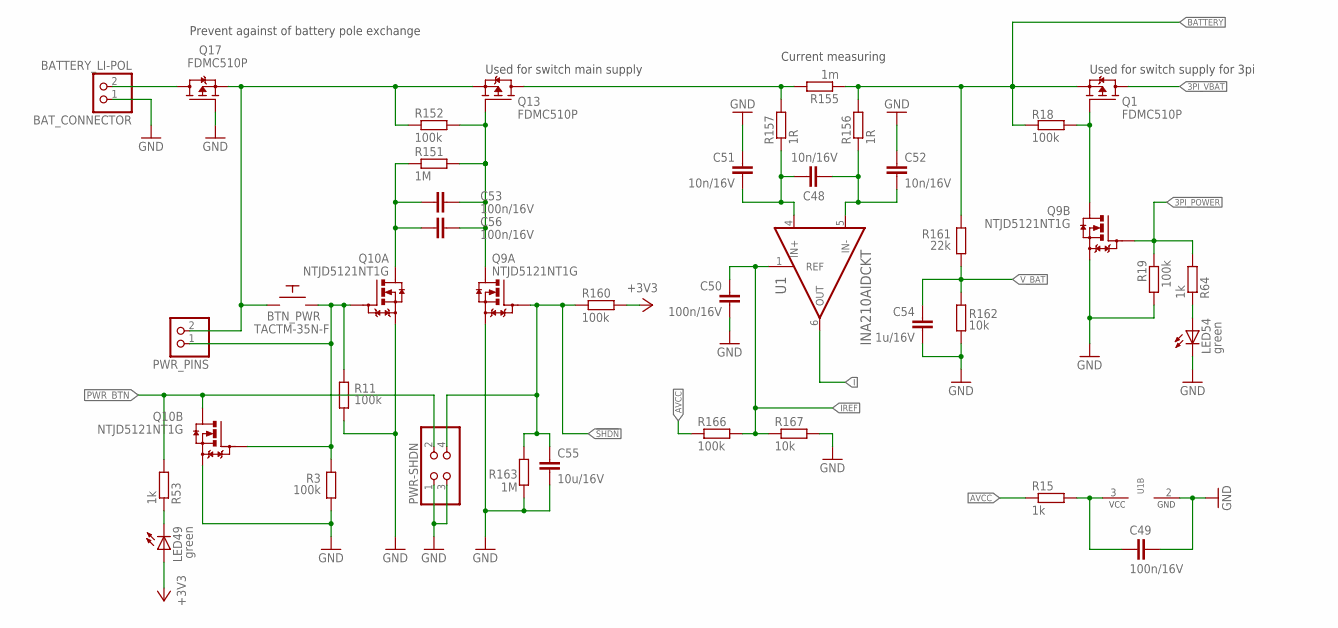
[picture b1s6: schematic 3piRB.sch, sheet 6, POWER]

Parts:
BAT_CONNECTOR: BATTERY_LI-POL; 1X02
BTN_PWR: TACTM-35N-F
C48, C51, C52: 10n/16V; C0402
C49, C50, C53, C56: 100n/16V; C0402
C54: 1u/16V; C0805
C55: 10u/16V; C0805
LED49, LED54: green; CHIPLED_0603
PWR-SHDN: PINHD-2X2; 2X02
PWR_PINS: PINHD-1X2; 1X02
Q1, Q13, Q17: FDMC510P; MLP3.3X3.3_HS
Q9, Q10: NTJD5121NT1G; SOT363
R3, R11, R18, R19, R152, R160, R166: 100k; _0402MP
R15, R53, R64: 1k; _0402MP
R151, R163: 1M; _0402MP
R155: 1m; 1206
R156, R157: 1R; _0402MP
R161: 22k; _0402MP
R162, R167: 10k; _0402MP
U1: INA210AIDCKT; SOT65P210X110-6N; MPN INA210AIDCKT

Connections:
3PI_POWER: Q9.5 (G), R19.1, R64.2; also elsewhere on the board
3PI_VBAT: Q1.5 (D), Q1.6 (D), Q1.7 (D), Q1.8 (D); also elsewhere on the board
3_PI_POWER_H_GATE: Q1.4 (G), Q9.3 (D), R18.2
!SHDN: C55.2, PWR-SHDN.4, Q9.2 (G), R160.1, R163.2; also elsewhere on the board
+3V3: LED49.A, R160.2; also elsewhere on the board
AVCC: R15.1, R166.1; also elsewhere on the board
BATTERY: Q1.1 (S), Q1.2 (S), Q1.3 (S), R18.1, R155.1, R156.2, R161.2; also elsewhere on the board
BATTERY_BEHIND_SWITCH: Q13.5 (D), Q13.6 (D), Q13.7 (D), Q13.8 (D), R155.2, R157.2
BATTERY_CONNECTOR: BAT_CONNECTOR.2, Q17.5 (D), Q17.6 (D), Q17.7 (D), Q17.8 (D)
BATTERY_REVERSE_PROTECTED: BTN_PWR.P$4, PWR_PINS.2, Q13.1 (S), Q13.2 (S), Q13.3 (S), Q17.1 (S), Q17.2 (S), Q17.3 (S), R152.2
BTN_PWR_: BTN_PWR.P$2, PWR_PINS.1, Q10.2 (G), Q10.5 (G), R3.2, R11.2
GND: BAT_CONNECTOR.1, C49.1, C50.1, C51.2, C52.2, C54.2, C55.1, LED54.C, PWR-SHDN.1, PWR-SHDN.3, Q9.1 (S), Q9.4 (S), Q10.1 (S), Q10.4 (S), Q17.4 (G), R3.1, R11.1, R19.2, R162.1, R163.1, R167.2, U1.2 (GND); also elsewhere on the board
I: U1.6 (OUT); also elsewhere on the board
IREF: C50.2, R166.2, R167.1, U1.1 (REF); also elsewhere on the board
I_AMP_PWR: C49.2, R15.2, U1.3 (VCC)
I_IN+: C48.1, C51.1, R157.1, U1.4 (IN+)
I_IN-: C48.2, C52.1, R156.1, U1.5 (IN-)
LED_R_25: LED54.A, R64.1
unnamed: LED49.C, R53.1
ON_SW: C53.2, C56.2, Q10.6 (D), R151.2
PWR_BTN: PWR-SHDN.2, Q10.3 (D), R53.2; also elsewhere on the board
SW_GATE: C53.1, C56.1, Q9.6 (D), Q13.4 (G), R151.1, R152.1
V_BAT: C54.1, R161.1, R162.2; also elsewhere on the board

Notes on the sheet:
Used for switch supply for 3pi
Prevent against of battery pole exchange
Used for switch main supply
Current measuring

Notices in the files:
parts and their libraries:
microbuilder: This work is placed in the public domain, and may be freely used for commercial and non-commercial work with the following conditions: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
resistor-array: Copyright (C) 2008, Bob Starr
